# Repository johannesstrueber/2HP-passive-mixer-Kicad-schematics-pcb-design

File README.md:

# 2HP passive mixer Eurorack Module<br/> Work in Progress Schematics, PCBs, and Design Files 
This consits of very basic schematics and two pcb files. One for the frontpanel and the other for soldering the audio jacks. I also created two design files. The first is for matching the drill holes of the panel with the placed components. The second is for labeling the components on the silkscreen layer of the panel.

***This is a work-in-progress project. Take nothing for granted. The first revision is now produced*** 
<br/><br/>

**CHANGELOG** <br/>
<br/>

**rev 0.1** <br/>
<ul>
<li>first layout NOT PRODUCED. It's produced. Check the photo ;)</li>
</ul>

<br/>

**KICAD Notes**
 - design_placement.svg is placed on layer USER 8
 - circuit layout is generated by the freerouting plugin
<br/>

**Working Docs by** 
- [northcoastsynthesis - PDF](https://files.northcoastsynthesis.com/passivemult.pdf)
<br/>

**Fonts**
- [Rocko – Casady & Greene](https://moorstation.org/typoasis/designers/casady_greene/r_z.htm)
- [Tiny – Jack Halten Fahnestock](https://velvetyne.fr/fonts/tiny/)
<br/>

**Photo of the module**
<br/>
<br/>

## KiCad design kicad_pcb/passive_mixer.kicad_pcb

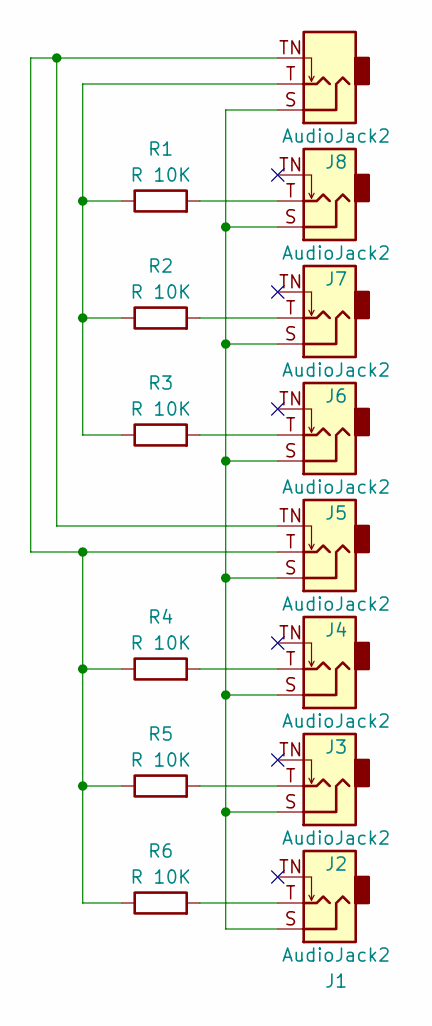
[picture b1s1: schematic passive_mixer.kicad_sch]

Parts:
J1, J2, J3, J4, J5, J6, J7, J8: AudioJack2; Jack_3.5mm_QingPu_WQP-PJ398SM_Vertical_CircularHoles
R1, R2, R3, R4, R5, R6: R 10K; R_Axial_DIN0204_L3.6mm_D1.6mm_P1.90mm_Vertical

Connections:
unnamed: J1.S, J2.S, J3.S, J4.S, J5.S, J6.S, J7.S, J8.S
unnamed: J1.T, R6.2
unnamed: J2.T, R5.2
unnamed: J3.T, R4.2
unnamed: J4.T, J4.TN, J8.TN, R4.1, R5.1, R6.1
unnamed: J5.T, R3.2
unnamed: J6.T, R2.2
unnamed: J7.T, R1.2
unnamed: J8.T, R1.1, R2.1, R3.1

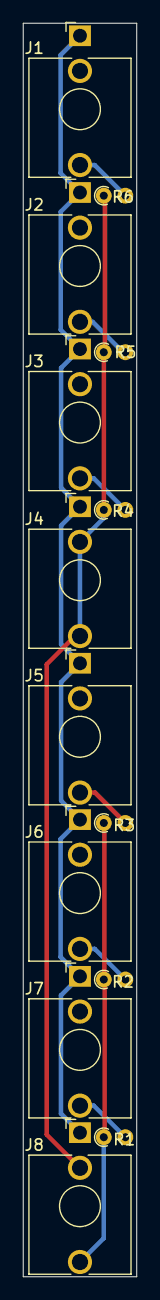
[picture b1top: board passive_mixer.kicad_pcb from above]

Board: 2 copper layers, 10.0 x 110.5 mm, 14 parts (0 on the bottom side), 9 nets.

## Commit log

2023-07-07 feat: :tada: init project
2023-07-07 screenshot
2023-07-07 typo
